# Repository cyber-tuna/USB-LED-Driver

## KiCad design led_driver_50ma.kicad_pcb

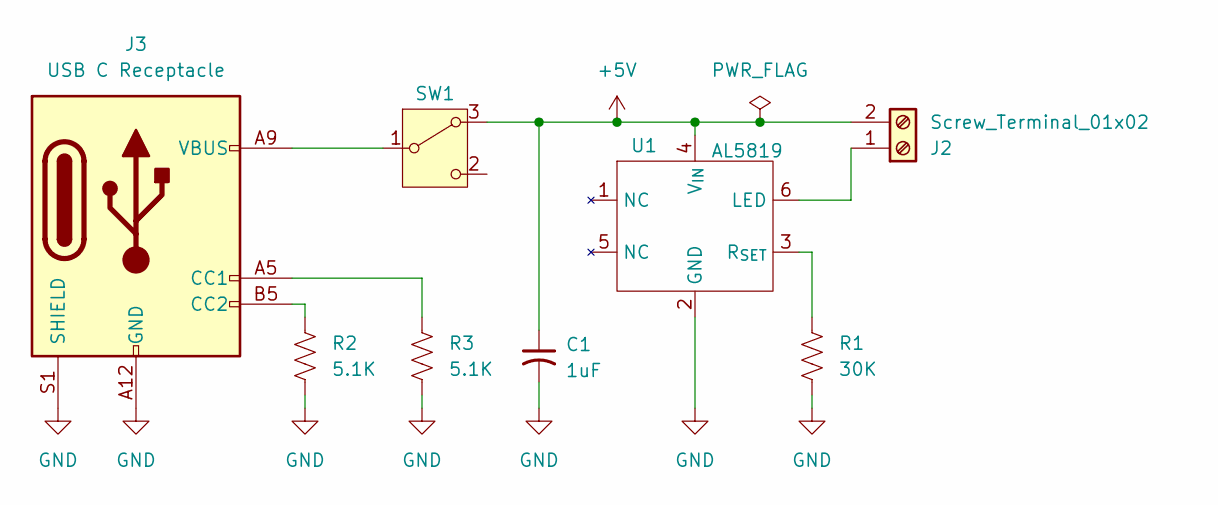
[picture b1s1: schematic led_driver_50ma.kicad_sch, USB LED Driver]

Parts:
C1: 1uF; C_1206_3216Metric
J2: Screw_Terminal_01x02; TerminalBlock_Phoenix_MPT-0,5-2-2.54_1x02_P2.54mm_Horizontal
J3: USB C Receptacle; USB_C_Receptacle_GCT_USB4125-xx-x_6P_TopMnt_Horizontal
R1: 30K; R_1206_3216Metric
R2, R3: 5.1K; R_1206_3216Metric
SW1: Slide Switch; SW_Slide-03_Wuerth-WS-SLTV_10x2.5x6.4_P2.54mm
U1: AL5819; SOT-23-6_Handsoldering

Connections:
+5V: C1.1, J2.2, SW1.3 (A), U1.4 (V_{IN})
GND: C1.2, J3.A12 (GND), J3.B12 (GND), J3.S1 (SHIELD), R1.2, R2.2, R3.2, U1.2 (GND)
unnamed: J2.1, U1.6 (LED)
unnamed: J3.A5 (CC1), R3.1
unnamed: J3.B5 (CC2), R2.1
unnamed: J3.A9 (VBUS), J3.B9 (VBUS), SW1.1 (B)
unnamed: R1.1, U1.3 (R_{SET})

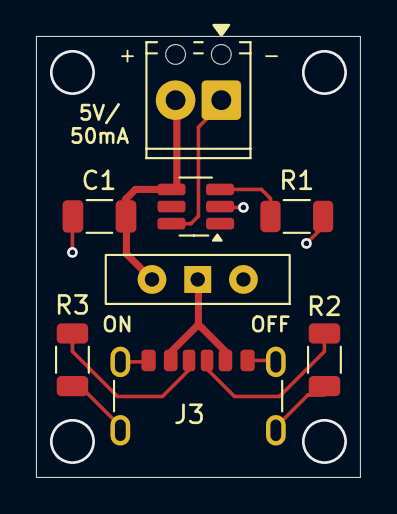
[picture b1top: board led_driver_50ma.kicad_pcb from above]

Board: 2 copper layers, 18.0 x 24.5 mm, 8 parts (0 on the bottom side), 7 nets.

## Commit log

2026-03-21 added rest of design files
2026-03-30 Use bottom layer ground pour and few other tweaks
2026-03-31 switch to USB c instead of usb micro
2026-04-05 finished making some connections
2026-04-06 updates to AL5819 symbol
